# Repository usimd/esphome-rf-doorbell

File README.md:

# ESPHome RF Doorbell

Battery-powered ESPHome doorbell hardware and firmware centered on the current Rev3 base board.

## Current Scope

- `base/` is the active hardware target.
- `esphome/doorbell.yaml` is the active firmware target.
- Rev3 uses ESP32-C6, LTC4079, ISL23315, MAX17260, and ESPHome's built-in `sx126x` support.
- `remote/` is intentionally kept as unfinished WIP hardware. It is not a supported production target.

## Rev3 Hardware Summary

| Ref | Part | Purpose |
|-----|------|---------|
| U1 | LTC4079 | Li-ion charger |
| U3 | TPS63900 | Low-power buck-boost regulator |
| U4 | MAX17260 | Fuel gauge |
| U5 | LTV-354T | Doorbell input optocoupler |
| U6 | G3VM-31DR | Door opener relay |
| U7 | Wio-SX1262 | SX1262 radio module |
| U8 | G3VM-63ER | Bell mute relay |
| U9 | ESP32-C6-MINI-1 | Main MCU |
| U10 | ISL23315 | Digipot for charger control |

The base board already includes an SX126x receive path and that remains part of the intended design, even though the remote side is still unfinished.

## Repository Layout

```text
base/                    Active Rev3 KiCad project
datasheets/              Datasheets and hardware notes used during development
esphome/                 Active ESPHome firmware
esphome/components/      Custom ESPHome components
lib/                     Project KiCad footprints and symbols
remote/                  Unfinished remote hardware kept as WIP
```

## Firmware

The active firmware is in `esphome/doorbell.yaml`: an always-connected Thread SED
with automatic light sleep, targeting ESPHome 2026.11.0b3. WiFi/deep-sleep firmware
remains available in git history.

Implemented custom components:

- `doorbell_controller`: charger control, supply sensing, direct bell mute and light-sleep GPIO wake
- `max17260`: fuel gauge driver with POR handling and learned-parameter persistence

Radio support uses ESPHome's built-in `sx126x` component rather than a custom RF stack.

## Build

Install the pinned beta toolchain, then build:

```bash
.venv/bin/python -m pip install -r esphome/requirements.txt
.venv/bin/esphome compile esphome/doorbell.yaml
```

The configuration expects `esphome/secrets.yaml` to contain a real `thread_tlv`
dataset, API encryption key and OTA password. See [firmware setup](esphome/README.md).

## Status

- Legacy firmware and custom components are removed from the supported path.
- Thread firmware requires hardware bring-up and current measurement before deployment.
- CI builds the Rev3 firmware and the base KiCad project.
- `remote/` remains a hardware placeholder for future work and still contains legacy symbols/footprints inside that WIP design.

## Notes

- The ESP32-C6 pin usage in this design currently triggers ESPHome warnings for USB-Serial-JTAG pins and strapping pins. Those warnings reflect the current hardware choices and should be kept in mind during bring-up.
- `esphome/charging_test.yaml` and `esphome/charging_test_simple.yaml` currently exist as untracked placeholders and are not part of the supported firmware path.

## AISLER discount

In case you want to order this (or any other) project at AISLER, here's a 10€ discount code: `MakeInEurope-ZDCTN`

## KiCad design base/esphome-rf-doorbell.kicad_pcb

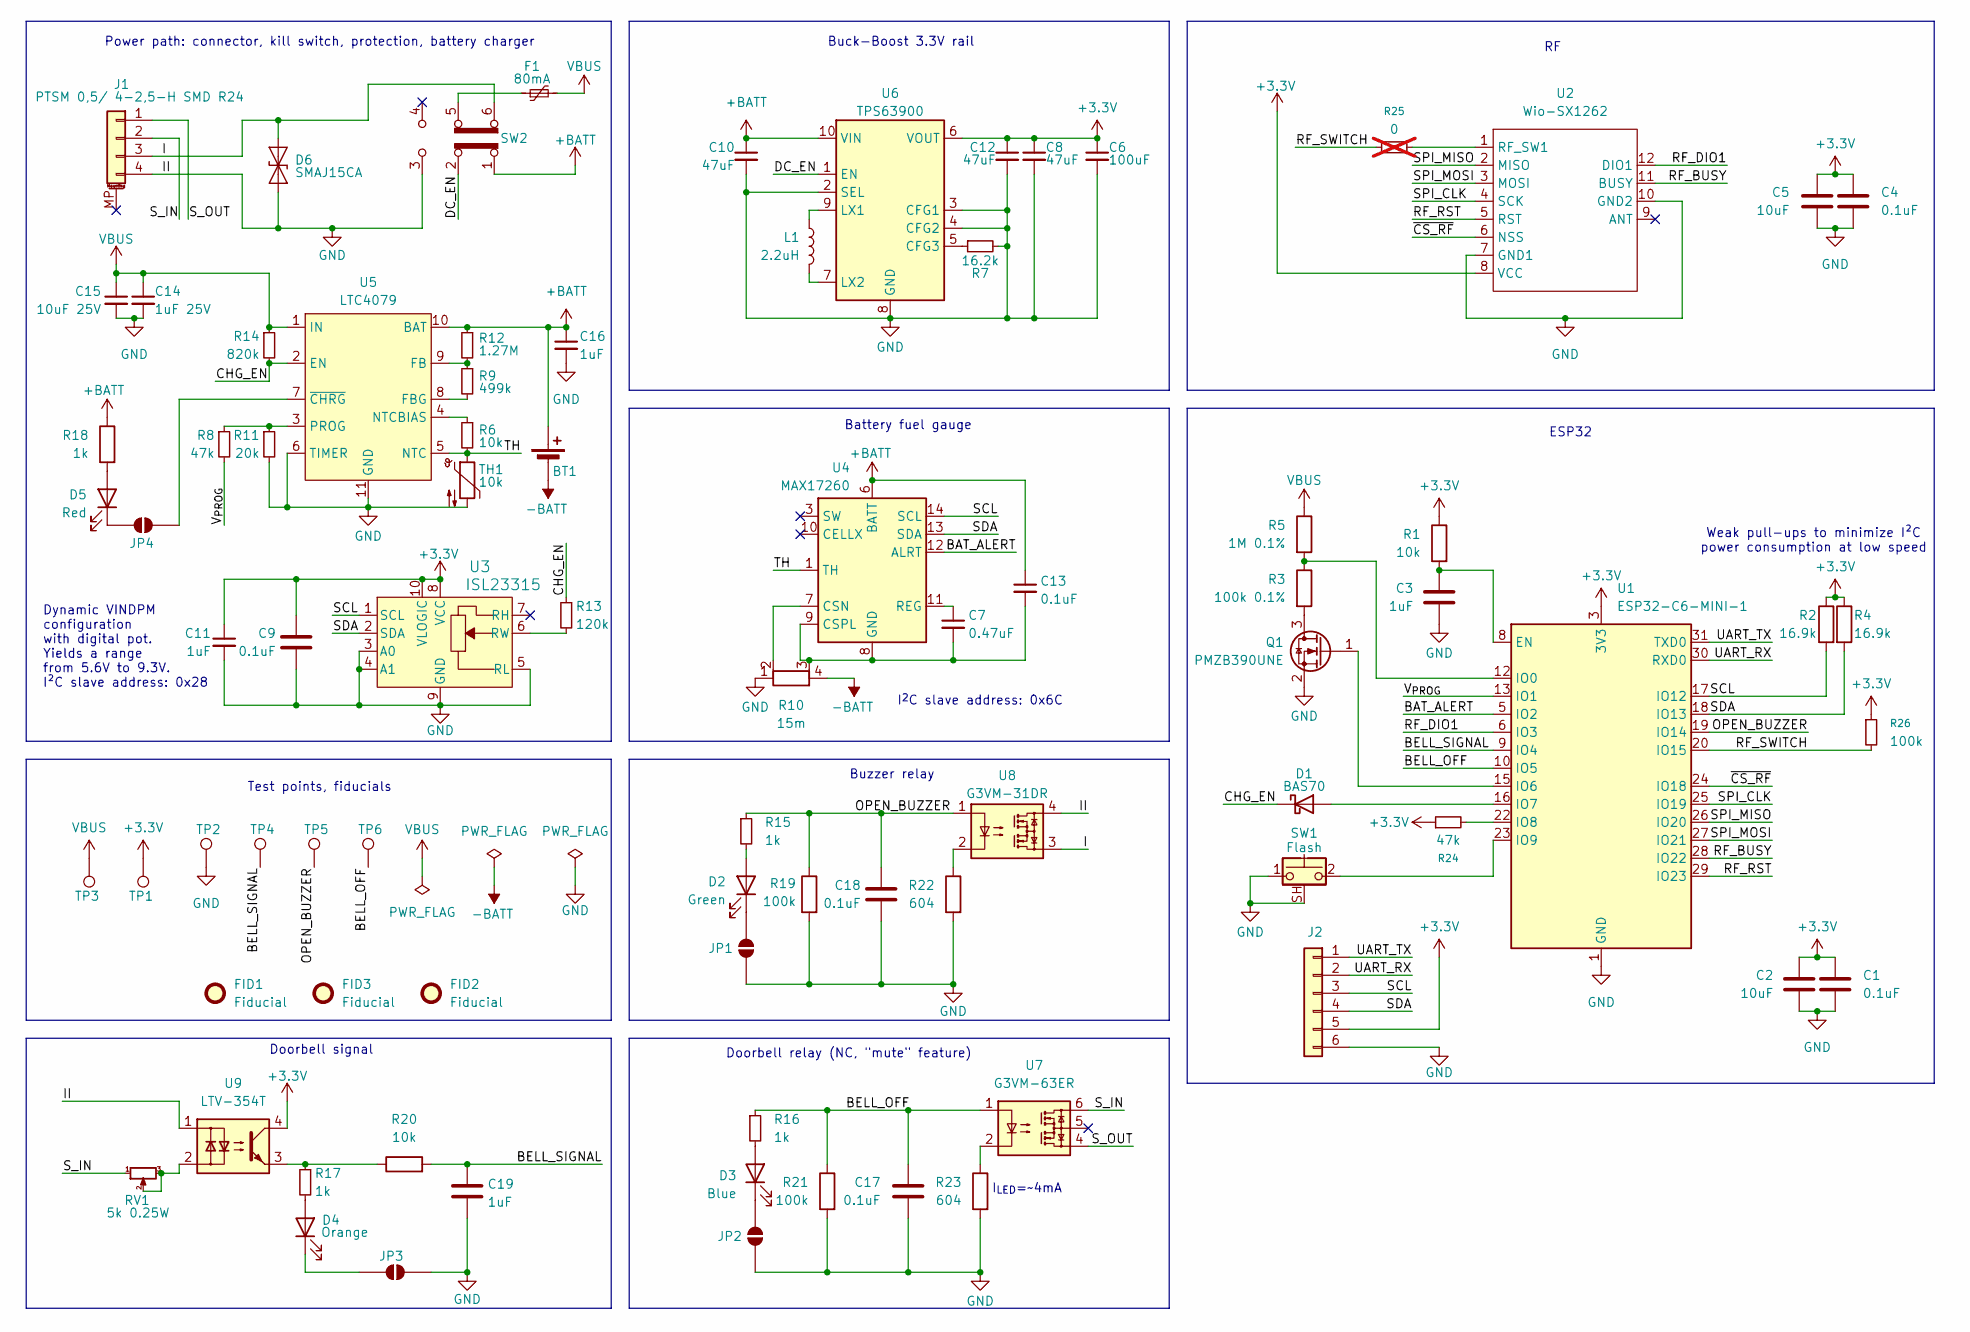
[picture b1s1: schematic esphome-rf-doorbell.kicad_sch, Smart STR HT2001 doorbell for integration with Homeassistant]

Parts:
BT1: Molex_PicoBlade_53261-0271_1x02-1MP_P1.25mm_Horizontal; MPN 532610271
C1, C4, C9, C13, C17, C18: 0.1uF; C_0402_1005Metric
C2, C5: 10uF; C_0603_1608Metric
C3: 1uF; C_0603_1608Metric
C6: 100uF; C_1206_3216Metric
C7: 0.47uF; C_0402_1005Metric
C8, C10, C12: 47uF; C_0805_2012Metric
C11, C16, C19: 1uF; C_0402_1005Metric
C14: 1uF 25V; C_0402_1005Metric
C15: 10uF 25V; C_0603_1608Metric
D1: BAS70; D_SOD-523; MPN BAS7002VH6327XTSA1
D2: Green; LED_0603_1608Metric
D3: Blue; LED_0603_1608Metric
D4: Orange; LED_0603_1608Metric
D5: Red; LED_0603_1608Metric
D6: SMAJ15CA; D_SMA; MPN SMAJ15CA
F1: 80mA; Fuse_0603_1608Metric; MPN SMD0603B008TF
FID1, FID2, FID3: Fiducial; Fiducial_0.5mm_Mask1mm
J1: PTSM 0,5/ 4-2,5-H SMD R24; PHOENIX_1702474; MPN 1702474
J2: Conn_01x06; Connector_PogoClamp_1.27mm
JP1, JP2, JP3, JP4: SolderJumper_2_Open; SolderJumper-2_P1.3mm_Open_RoundedPad1.0x1.5mm
L1: 2.2uH; L_1210_3225Metric; MPN DFE32CAH2R2MR0L
Q1: PMZB390UNE; Diodes_DFN1006-3; MPN PMZB390UNEYL
R1: 10k; R_0603_1608Metric
R2, R4: 16.9k; R_0402_1005Metric
R3: 100k 0.1%; C_0402_1005Metric
R5: 1M 0.1%; C_0402_1005Metric
R6, R20: 10k; R_0402_1005Metric
R7: 16.2k; R_0402_1005Metric
R8: 47k; R_0402_1005Metric
R9: 499k; R_0402_1005Metric
R10: 15m; R_Shunt_D1WRL1206; MPN D1WRL1206L4R015D-T5
R11: 20k; R_0402_1005Metric
R12: 1.27M; R_0402_1005Metric
R13: 120k; R_0402_1005Metric
R14: 820k; R_0805_2012Metric
R15, R16, R17, R18: 1k; R_0402_1005Metric
R19, R21: 100k; R_0402_1005Metric
R22, R23: 604; R_0402_1005Metric
R24: 47k; C_0402_1005Metric
R25: 0; C_0402_1005Metric; not fitted
R26: 100k; C_0402_1005Metric
RV1: 5k 0.25W; Potentiometer_Bourns_3214W_Vertical; MPN 3214W-1-502E
SW1: Flash; SW_SPST_Panasonic_EVQPL_3PL_5PL_PT_A08; MPN TVCU18015BPB
SW2: CL-SB-22A-11T; CL-SB-22A; MPN CL-SB-22A-11T
TH1: 10k; R_0603_1608Metric; MPN NTCS0603E3103FLT
TP1, TP2, TP3, TP4, TP5, TP6: TestPoint; TestPoint_Pad_D1.5mm
U1: ESP32-C6-MINI-1; XCVR_ESP32-C6-MINI-1U-N4; MPN ESP32-C6-MINI-1U-N4
U2: Wio-SX1262; Wio-SX1262 PCB Package; MPN WIO-SX1262
U3: ISL23315; L10_2P1X1P6A_INR; MPN ISL23315TFRUZ-T7A
U4: MAX17260; TDFN-14-1EP_3x3mm_P0.4mm_EP1.78x2.35mm; MPN MAX17260SETD+
U5: LTC4079; DFN-10-1EP_3x3mm_P0.5mm_EP1.65x2.38mm; MPN LTC4079EDD#TRPBF
U6: TPS63900; WSON-10-1EP_2.5x2.5mm_P0.5mm_EP1.2x2mm_ThermalVias; MPN TPS63900DSKR
U7: G3VM-63ER; G3VM-21ER; MPN G3VM-63ER
U8: G3VM-31DR; G3VM-21DR; MPN G3VM-31DR
U9: LTV-354T; SO-4_4.4x3.6mm_P2.54mm; MPN LTV-354T

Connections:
+3.3V: C1.1, C2.1, C4.1, C5.1, C6.1, C8.1, C9.1, C11.1, C12.1, J2.5, R1.1, R2.1, R4.1, R24.1, R26.1, TP1.1 (1_1), U1.3 (3V3), U2.8 (VCC), U3.8 (VCC), U3.10 (VLOGIC), U6.6 (VOUT), U9.4
+BATT: BT1.1 (+), C10.1, C13.1, C16.1, R12.1, R18.1, SW2.1 (A), U4.6 (BATT), U5.10 (BAT), U6.10 (VIN)
-BATT: BT1.2 (-), R10.4
/BAT_ALERT: U1.5 (IO2), U4.12 (ALRT)
/BELL_OFF: C17.1, R16.1, R21.1, TP6.1 (1_1), U1.10 (IO5), U7.1
/BELL_SIGNAL: C19.1, R20.2, TP4.1 (1_1), U1.9 (IO4)
/CHG_EN: D1.1 (K), R13.1, R14.2, U5.2 (EN)
/DC_EN: SW2.2 (B), U6.1 (EN)
/I: D6.2 (A2), J1.3, SW2.6 (C), U8.3
/OPEN_BUZZER: C18.1, R15.1, R19.1, TP5.1 (1_1), U1.19 (IO14), U8.1
/RF_BUSY: U1.28 (IO22), U2.11 (BUSY)
/RF_DIO1: U1.6 (IO3), U2.12 (DIO1)
/RF_RST: U1.29 (IO23), U2.5 (RST)
/RF_SWITCH: R25.1, R26.2, U1.20 (IO15)
/SCL: J2.3, R2.2, U1.17 (IO12), U3.1 (SCL), U4.14 (SCL)
/SDA: J2.4, R4.2, U1.18 (IO13), U3.2 (SDA), U4.13 (SDA)
/SPI_CLK: U1.25 (IO19), U2.4 (SCK)
/SPI_MISO: U1.26 (IO20), U2.2 (MISO)
/SPI_MOSI: U1.27 (IO21), U2.3 (MOSI)
/S_IN: J1.2, RV1.1, U7.6
/S_OUT: J1.1, U7.4
/TH: R6.2, TH1.1, U4.1 (TH), U5.5 (NTC)
/UART_RX: J2.2, U1.30 (RXD0)
/UART_TX: J2.1, U1.31 (TXD0)
/V_{PROG}: R8.2, U1.13 (IO1)
/~CS_RF: U1.24 (IO18), U2.6 (NSS)
GND: C1.2, C2.2, C3.2, C4.2, C5.2, C6.2, C8.2, C9.2, C10.2, C11.2, C12.2, C14.2, C15.2, C16.2, C17.2, C18.2, C19.2, D6.1 (A1), J1.4, J2.6, JP1.1 (A), JP2.1 (A), JP3.2 (B), Q1.2 (S), R7.2, R10.1, R11.2, R19.2, R21.2, R22.2, R23.2, SW1.1, SW1.SH (B), SW2.3 (C), TH1.2, TP2.1 (1_1), U1.1 (GND), U1.2 (GND), U1.11 (GND), U1.14 (GND), U1.36 (GND), U1.37 (GND), U1.38 (GND), U1.39 (GND), U1.40 (GND), U1.41 (GND), U1.42 (GND), U1.43 (GND), U1.44 (GND), U1.45 (GND), U1.46 (GND), U1.47 (GND), U1.48 (GND), U1.49 (GND), U1.50 (GND), U1.51 (GND), U1.52 (GND), U1.53 (GND), U2.7 (GND1), U2.10 (GND2), U3.3 (A0), U3.4 (A1), U3.5 (RL), U3.9 (GND), U5.6 (TIMER), U5.11 (GND), U6.2 (SEL), U6.3 (CFG1), U6.4 (CFG2), U6.8 (GND), U6.11 (GND), U8.4, U9.1
unnamed: D1.2 (A), U1.16 (IO7)
unnamed: D2.2 (A), R15.2
unnamed: D2.1 (K), JP1.2 (B)
unnamed: D3.2 (A), R16.2
unnamed: D3.1 (K), JP2.2 (B)
unnamed: D4.2 (A), R17.2
unnamed: D4.1 (K), JP3.1 (A)
unnamed: D5.2 (A), R18.2
unnamed: D5.1 (K), JP4.2 (B)
unnamed: F1.1, SW2.5 (B)
unnamed: JP4.1 (A), U5.7 (~CHRG)
unnamed: Q1.3 (D), R3.2
unnamed: Q1.1 (G), U1.15 (IO6)
unnamed: R17.1, R20.1, U9.3
unnamed: R22.1, U8.2
unnamed: R23.1, U7.2
unnamed: RV1.2, RV1.3, U9.2
unnamed: C3.1, R1.2, U1.8 (EN)
unnamed: R3.1, R5.2, U1.12 (IO0)
unnamed: R24.2, U1.22 (IO8)
unnamed: SW1.2, U1.23 (IO9)
unnamed: R25.2, U2.1 (RF_SW1)
unnamed: R13.2, U3.6 (RW)
unnamed: R10.2, U4.7 (CSN)
unnamed: C7.2, C13.2, R10.3, U4.8 (GND), U4.9 (CSPL), U4.15 (GND)
unnamed: C7.1, U4.11 (REG)
unnamed: R9.1, R12.2, U5.9 (FB)
unnamed: R9.2, U5.8 (FBG)
unnamed: R6.1, U5.4 (NTCBIAS)
unnamed: R8.1, R11.1, U5.3 (PROG)
unnamed: R7.1, U6.5 (CFG3)
unnamed: L1.1, U6.9 (LX1)
unnamed: L1.2, U6.7 (LX2)
VBUS: C14.1, C15.1, F1.2, R5.1, R14.1, TP3.1 (1_1), U5.1 (IN)

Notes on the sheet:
Dynamic VINDPM configuration with digital pot. Yields a range from 5.6V to 9.3V. I²C slave address: 0x28
Test points, fiducials
Battery fuel gauge
ESP32
Weak pull-ups to minimize I²C power consumption at low speed
Doorbell signal
I_{LED}=~4mA
Buzzer relay
Doorbell relay (NC, "mute" feature)
Buck-Boost 3.3V rail
Power path: connector, kill switch, protection, battery charger
I^{2}C slave address: 0x6C

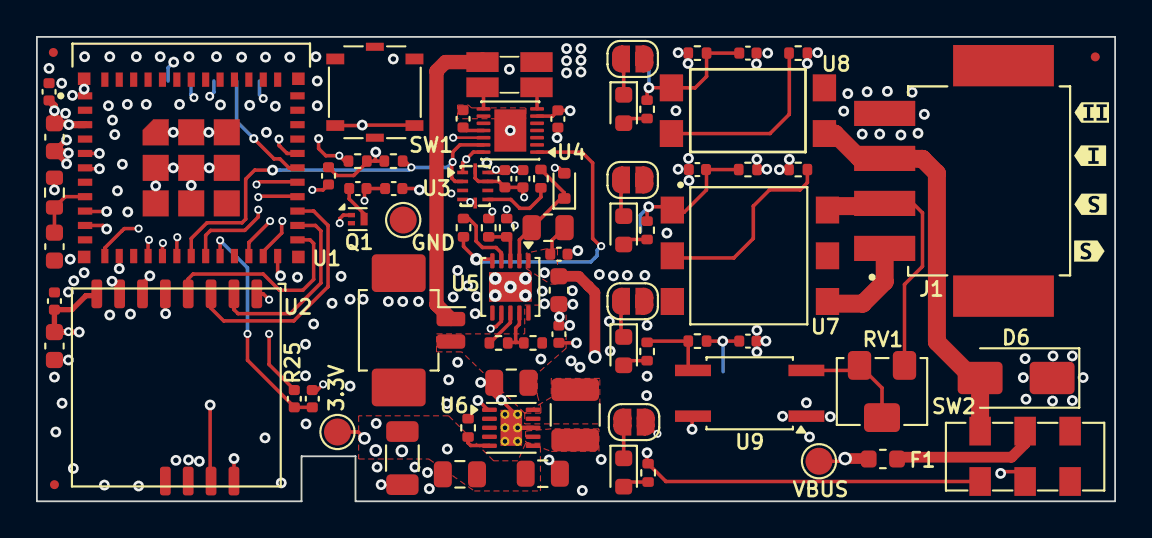
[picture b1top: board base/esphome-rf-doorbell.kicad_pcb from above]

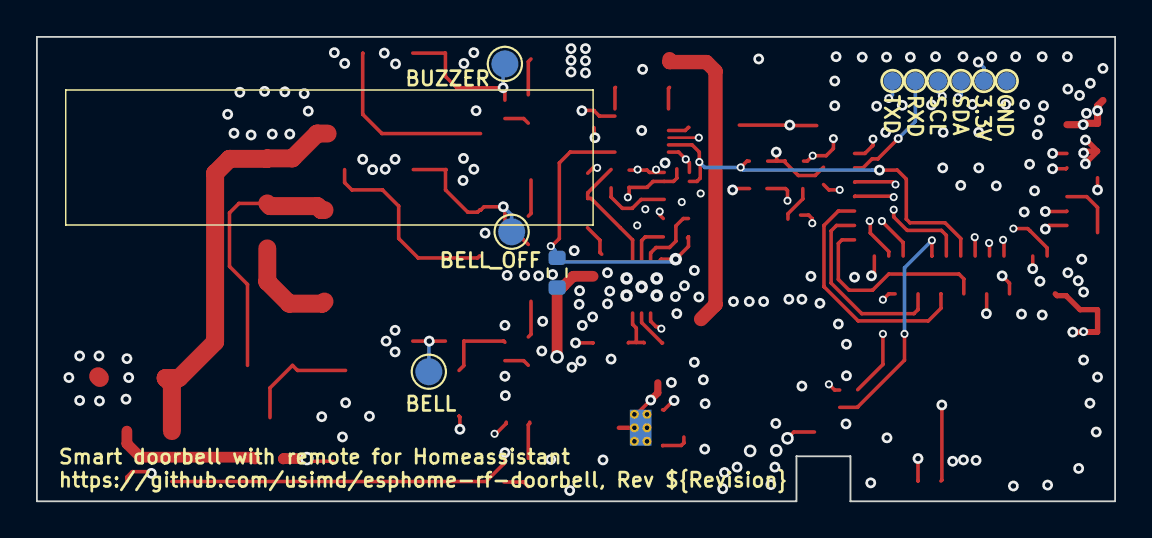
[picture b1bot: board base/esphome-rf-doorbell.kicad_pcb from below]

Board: 4 copper layers, 59.9 x 25.8 mm, 87 parts (5 on the bottom side), 61 nets.

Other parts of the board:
kibuzzard-696E5F1B: G***; kibuzzard-696E5F1B
kibuzzard-696E5F3B: G***; kibuzzard-696E5F3B
kibuzzard-696E5F26: G***; kibuzzard-696E5F26
kibuzzard-696E5F32: G***; kibuzzard-696E5F32

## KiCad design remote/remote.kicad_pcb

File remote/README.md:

# Remote WIP

`remote/` is intentionally kept as unfinished hardware work.

- It is not a supported production target.
- The old remote firmware implementation was removed.
- The current schematic and PCB may still contain legacy placeholder parts from earlier RF exploration.
- Keep this directory as hardware WIP until the remote architecture is redesigned around the current project direction.

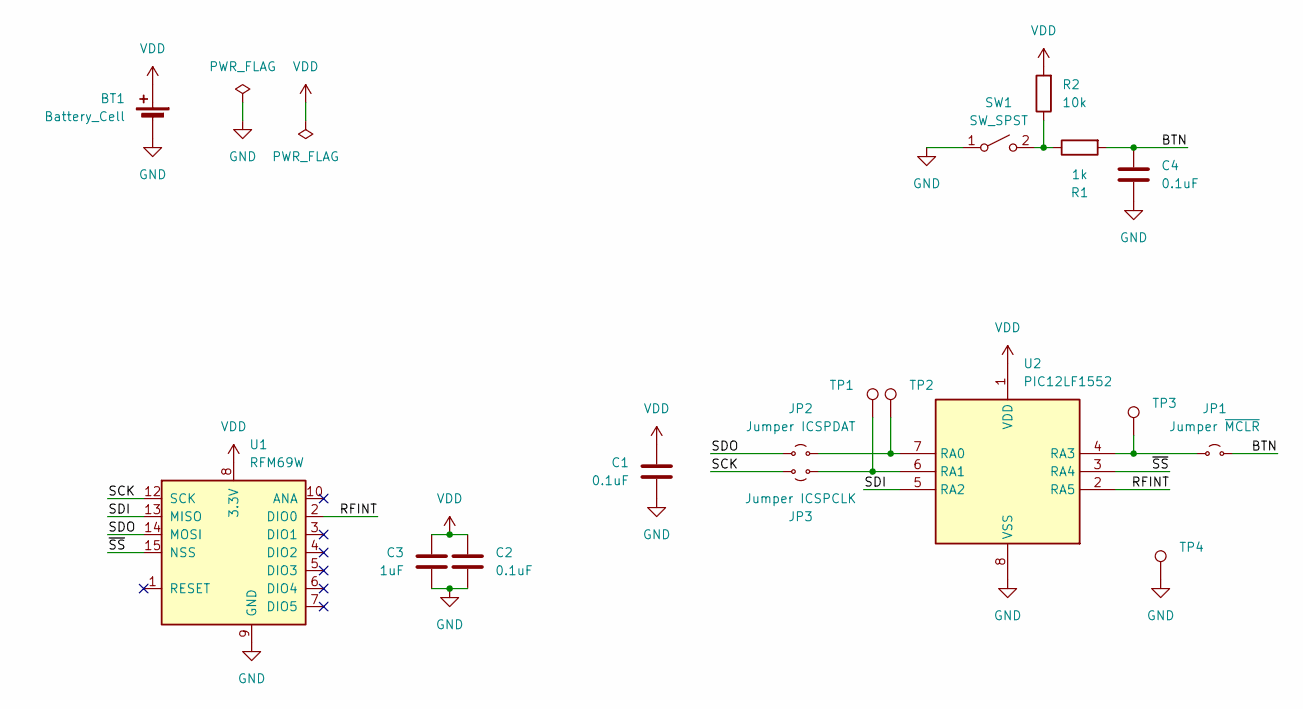
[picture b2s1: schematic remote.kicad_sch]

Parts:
BT1: Battery_Cell; BatteryHolder_Keystone_1060_1x2032
C1, C2, C4: 0.1uF; C_0603_1608Metric_Pad1.08x0.95mm_HandSolder
C3: 1uF; C_0603_1608Metric_Pad1.08x0.95mm_HandSolder
JP1: Jumper ~{MCLR}; SolderJumper-2_P1.3mm_Open_RoundedPad1.0x1.5mm
JP2: Jumper ICSPDAT; SolderJumper-2_P1.3mm_Open_RoundedPad1.0x1.5mm
JP3: Jumper ICSPCLK; SolderJumper-2_P1.3mm_Open_RoundedPad1.0x1.5mm
R1: 1k; R_0603_1608Metric_Pad0.98x0.95mm_HandSolder
R2: 10k; R_0603_1608Metric_Pad0.98x0.95mm_HandSolder
SW1: SW_SPST; SW_SPST_Panasonic_EVQPL_3PL_5PL_PT_A15
TP1, TP2, TP3, TP4: TestPoint; TestPoint_Keystone_5000-5004_Miniature
U1: RFM69W; HOPERF_RFM69HW
U2: PIC12LF1552; MSOP-8_3x3mm_P0.65mm

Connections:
/BTN: C4.1, JP1.2 (B), R1.2
/RFINT: U1.2 (DIO0), U2.2 (RA5)
/SCK: JP3.1 (A), U1.12 (SCK)
/SDI: U1.13 (MISO), U2.5 (RA2)
/SDO: JP2.1 (A), U1.14 (MOSI)
/~SS: U1.15 (NSS), U2.3 (RA4)
GND: BT1.2 (-), C1.2, C2.2, C3.2, C4.2, SW1.1 (A), TP4.1, U1.9 (GND), U1.11 (GND), U2.8 (VSS)
unnamed: JP1.1 (A), TP3.1, U2.4 (RA3)
unnamed: JP2.2 (B), TP2.1, U2.7 (RA0)
unnamed: JP3.2 (B), TP1.1, U2.6 (RA1)
unnamed: R1.1, R2.1, SW1.2 (B)
VDD: BT1.1 (+), C1.1, C2.1, C3.1, R2.2, U1.8 (3.3V), U2.1 (VDD)

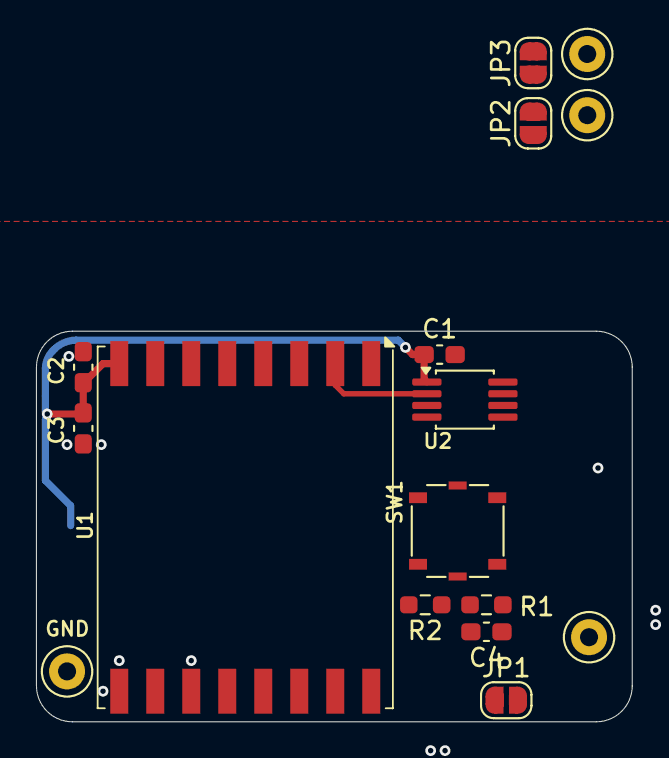
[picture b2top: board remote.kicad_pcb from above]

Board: 2 copper layers, 33.1 x 21.7 mm, 17 parts (1 on the bottom side), 12 nets.

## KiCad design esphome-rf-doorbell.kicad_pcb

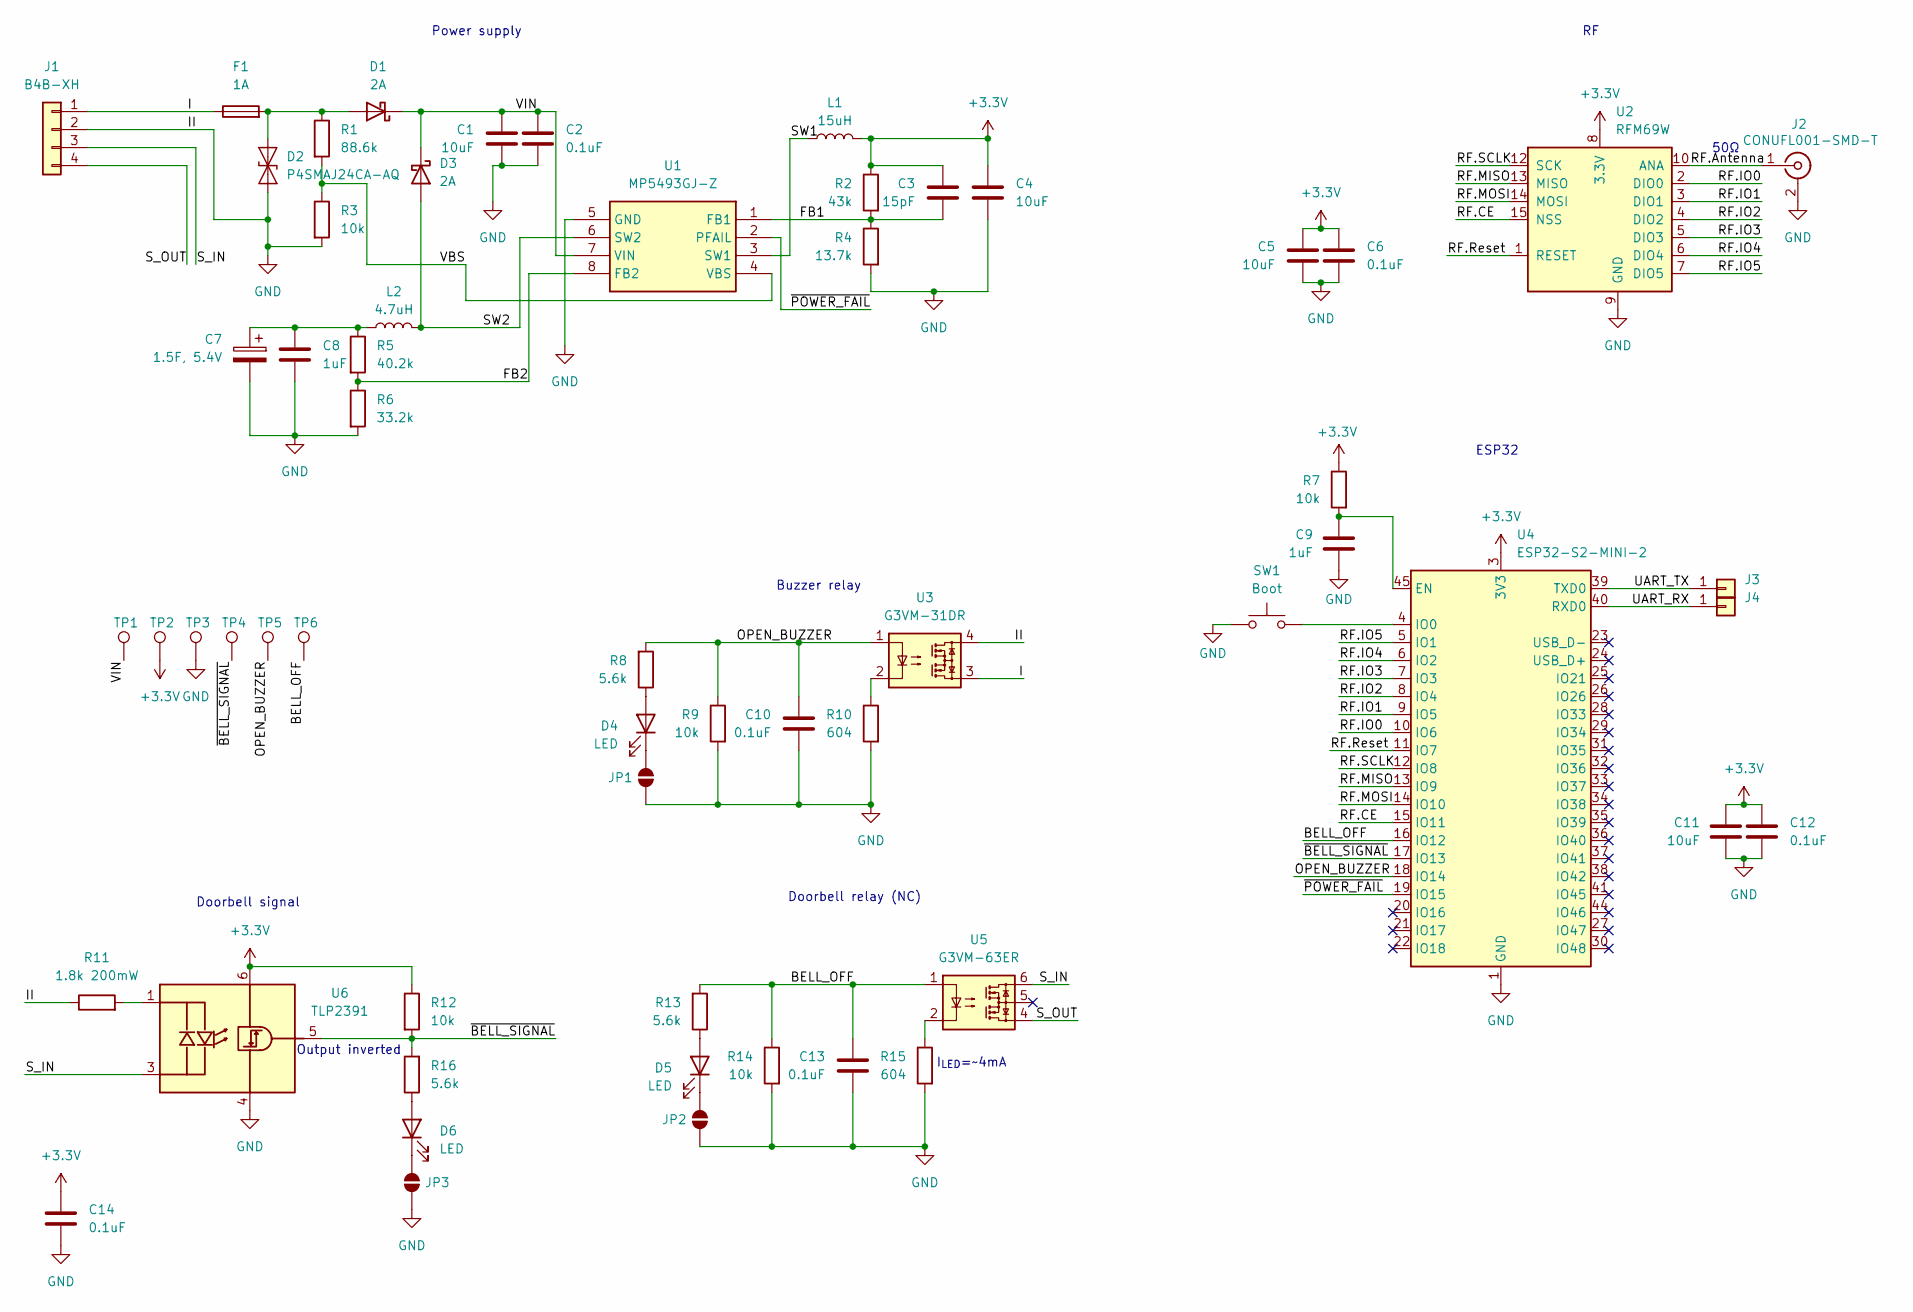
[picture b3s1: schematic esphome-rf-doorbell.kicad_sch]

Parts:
C1: 10uF; C_0805_2012Metric
C2, C6, C10, C12, C13, C14: 0.1uF; C_0402_1005Metric
C3: 15pF; R_0402_1005Metric
C4, C5, C11: 10uF; C_0603_1608Metric
C7: 1.5F, 5.4V; PHV5R4V155R; MPN PHV-5R4V155-R
C8: 1uF; R_0603_1608Metric
C9: 1uF; C_0603_1608Metric
D1, D3: 2A; D_SMA; MPN STPS2L60A
D2: P4SMAJ24CA-AQ; D_SMA; MPN P4SMAJ24CA-AQ
D4, D5, D6: LED; LED_0603_1608Metric
F1: 1A; Fuse_0603_1608Metric; MPN 3412.0115.11
J1: B4B-XH; JST_XH_B4B-XH-A_1x04_P2.50mm_Vertical
J2: CONUFL001-SMD-T; U.FL_Hirose_U.FL-R-SMT-1_Vertical; MPN CONUFL001-SMD-T; LCSC Part # C22418213
J3, J4: Conn_01x01; TestPoint_Keystone_5000-5004_Miniature
JP1, JP2, JP3: SolderJumper_2_Open; SolderJumper-2_P1.3mm_Bridged_RoundedPad1.0x1.5mm
L1: 15uH; L_APV_ANR8040; MPN DJNR8040-150
L2: 4.7uH; L_APV_APH1040; MPN HPI1040-150
R1: 88.6k; R_0603_1608Metric
R2: 43k; R_0603_1608Metric
R3, R7, R9, R12, R14: 10k; R_0603_1608Metric
R4: 13.7k; R_0603_1608Metric
R5: 40.2k; R_0402_1005Metric
R6: 33.2k; R_0603_1608Metric
R8, R13, R16: 5.6k; R_0603_1608Metric
R10, R15: 604; R_0402_1005Metric_Pad0.72x0.64mm_HandSolder
R11: 1.8k 200mW; R_0603_1608Metric
SW1: Boot; SW_SPST_PTS647_Sx50; MPN TS110926045
TP1, TP2, TP3, TP4, TP5, TP6: TestPoint; TestPoint_Pad_D1.5mm
U1: MP5493GJ-Z; SOT65P280X100-8N; Manufacturer_Part_Number MP5493GJ-Z
U2: RFM69W; HOPERF_RFM69HW
U3: G3VM-31DR; SMDIP-4_W7.62mm
U4: ESP32-S2-MINI-2; ESP32-S2-MINI-1
U5: G3VM-63ER; SMDIP-6_W7.62mm; MPN G3VM-63ER
U6: TLP2391; OPTO_TLP2367_TPR_E; MPN TLP2391

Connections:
+3.3V: C3.1, C4.1, C5.1, C6.1, C11.1, C12.1, C14.1, L1.2, R2.1, R7.1, R12.1, TP2.1, U2.8 (3.3V), U4.3 (3V3), U6.6 (VDD)
/BELL_OFF: C13.1, R13.2, R14.1, TP6.1, U4.16 (IO12), U5.1
/FB1: C3.2, R2.2, R4.1, U1.1 (FB1)
/FB2: R5.2, R6.1, U1.8 (FB2)
/I: F1.1, J1.1, U3.3
/OPEN_BUZZER: C10.1, R8.2, R9.1, TP5.1, U3.1, U4.18 (IO14)
/RF.Antenna: J2.1 (In), U2.10 (ANA)
/RF.CE: U2.15 (NSS), U4.15 (IO11)
/RF.IO0: U2.2 (DIO0), U4.10 (IO6)
/RF.IO1: U2.3 (DIO1), U4.9 (IO5)
/RF.IO2: U2.4 (DIO2), U4.8 (IO4)
/RF.IO3: U2.5 (DIO3), U4.7 (IO3)
/RF.IO4: U2.6 (DIO4), U4.6 (IO2)
/RF.IO5: U2.7 (DIO5), U4.5 (IO1)
/RF.MISO: U2.13 (MISO), U4.13 (IO9)
/RF.MOSI: U2.14 (MOSI), U4.14 (IO10)
/RF.Reset: U2.1 (RESET), U4.11 (IO7)
/RF.SCLK: U2.12 (SCK), U4.12 (IO8)
/SW1: L1.1, U1.3 (SW1)
/SW2: D3.2 (A), L2.2, U1.6 (SW2)
/S_IN: J1.3, U5.6, U6.3 (K)
/S_OUT: J1.4, U5.4
/UART_RX: J4.1, U4.40 (RXD0)
/UART_TX: J3.1, U4.39 (TXD0)
/VBS: R1.2, R3.1, U1.4 (VBS)
/VIN: C1.1, C2.1, D1.1 (K), D3.1 (K), TP1.1, U1.7 (VIN)
/~BELL_SIGNAL: R12.2, R16.2, TP4.1, U4.17 (IO13), U6.5 (VO)
/~POWER_FAIL: U1.2 (PFAIL), U4.19 (IO15)
GND: C1.2, C2.2, C4.2, C5.2, C6.2, C7.2, C8.2, C9.2, C10.2, C11.2, C12.2, C13.2, C14.2, D2.1 (A1), J1.2, J2.2 (Ext), JP1.1 (A), JP2.1 (A), JP3.1 (A), R3.2, R4.2, R6.2, R9.2, R10.2, R11.1, R14.2, R15.2, SW1.1, TP3.1, U1.5 (GND), U2.9 (GND), U2.11 (GND), U3.4, U4.1 (GND), U4.2 (GND), U4.42 (GND), U4.43 (GND), U4.46 (GND), U4.47 (GND), U4.48 (GND), U4.49 (GND), U4.50 (GND), U4.51 (GND), U4.52 (GND), U4.53 (GND), U4.54 (GND), U4.55 (GND), U4.56 (GND), U4.57 (GND), U4.58 (GND), U4.59 (GND), U4.60 (GND), U4.61 (GND), U4.62 (GND), U4.63 (GND), U4.64 (GND), U4.65 (GND), U6.4 (GND)
unnamed: C7.1, C8.1, L2.1, R5.1
unnamed: D1.2 (A), D2.2 (A2), F1.2, R1.1
unnamed: D4.2 (A), R8.1
unnamed: D4.1 (K), JP1.2 (B)
unnamed: D5.2 (A), R13.1
unnamed: D5.1 (K), JP2.2 (B)
unnamed: D6.2 (A), R16.1
unnamed: D6.1 (K), JP3.2 (B)
unnamed: R10.1, U3.2
unnamed: R15.1, U5.2
unnamed: C9.1, R7.2, U4.45 (EN)
unnamed: SW1.2, U4.4 (IO0)
unnamed: R11.2, U6.1 (A)

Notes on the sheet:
ESP32
Doorbell signal
I_{LED}=~4mA
Buzzer relay
Doorbell relay (NC)
Output inverted
Power supply
50Ω

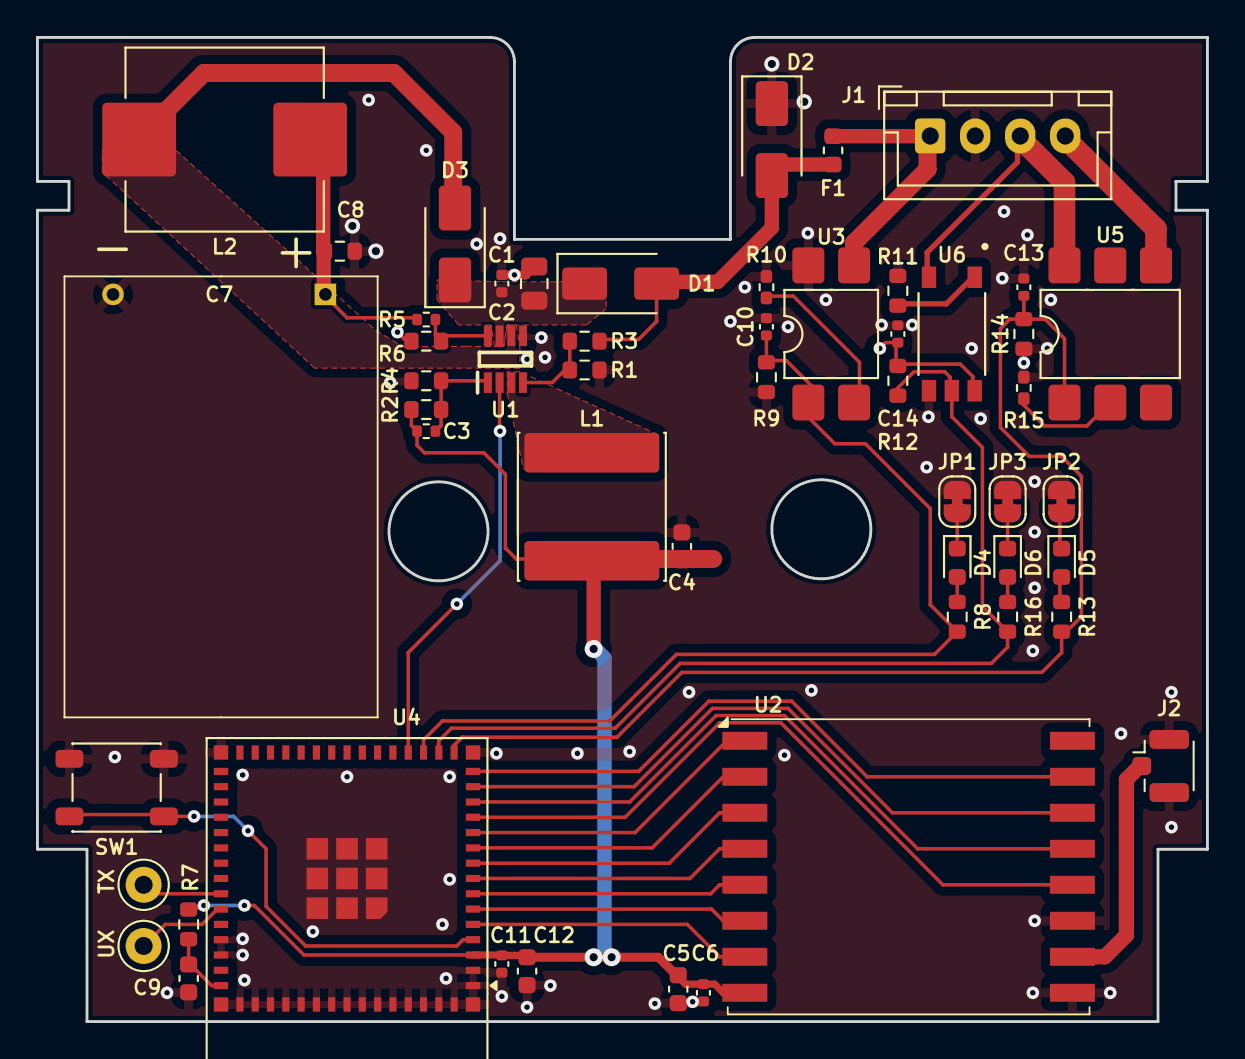
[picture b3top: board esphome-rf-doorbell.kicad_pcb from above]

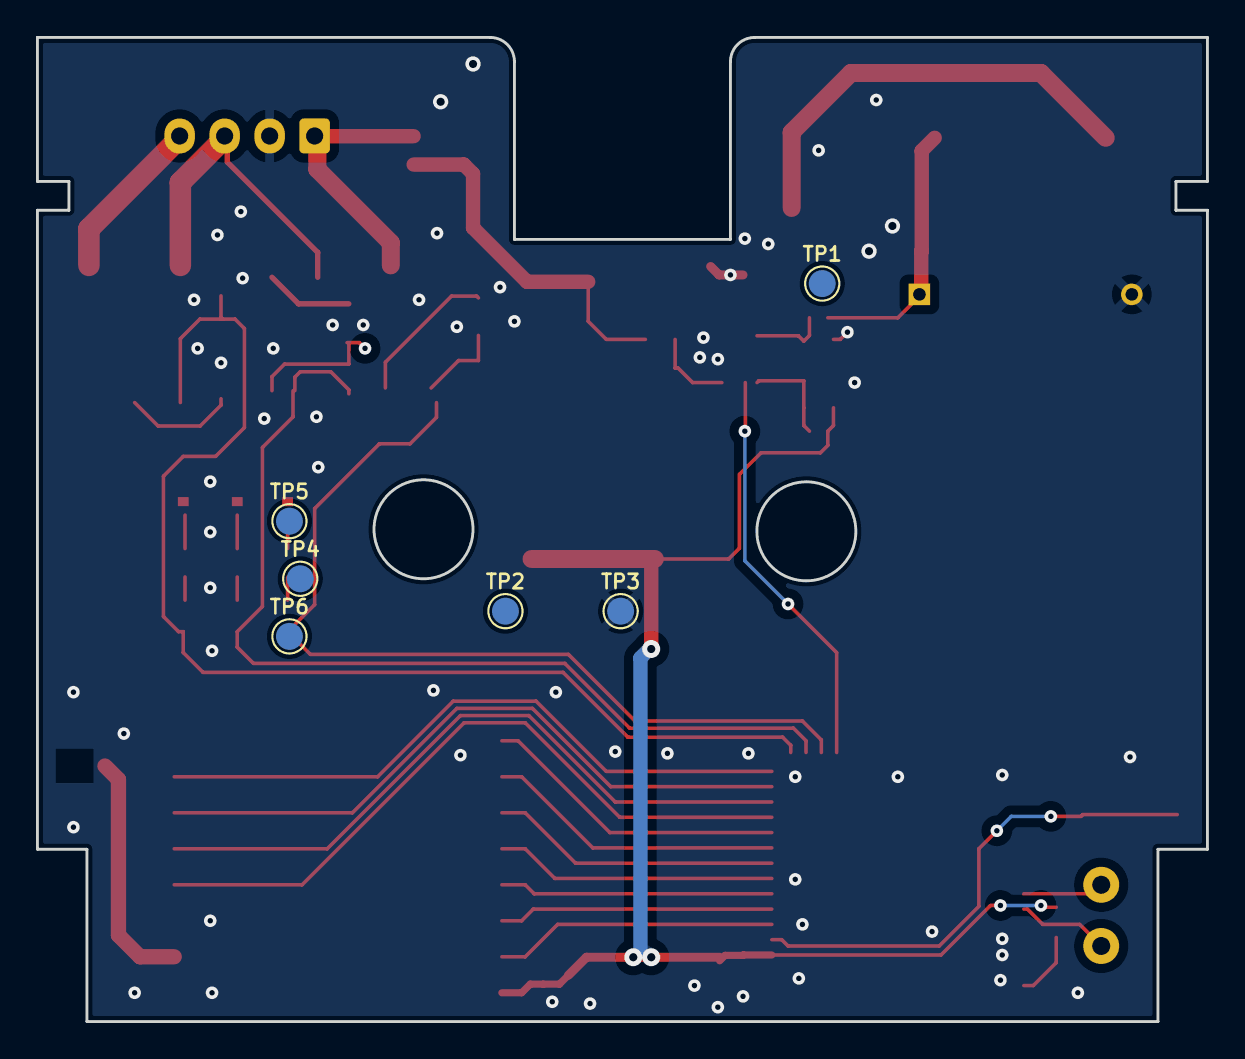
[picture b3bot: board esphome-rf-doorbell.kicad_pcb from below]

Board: 2 copper layers, 65.0 x 54.7 mm, 59 parts (6 on the bottom side), 42 nets.

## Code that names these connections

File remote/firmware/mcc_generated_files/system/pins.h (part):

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// get/set IO_RA0 aliases
#define IO_RA0_TRIS                 TRISAbits.TRISA0
#define IO_RA0_LAT                  LATAbits.LATA0
#define IO_RA0_PORT                 PORTAbits.RA0
#define IO_RA0_WPU                  WPUAbits.WPUA0
#define IO_RA0_OD                   ODCONAbits.
#define IO_RA0_ANS                  ANSELAbits.ANSA0
#define IO_RA0_SetHigh()            do { LATAbits.LATA0 = 1; } while(0)
#define IO_RA0_SetLow()             do { LATAbits.LATA0 = 0; } while(0)
#define IO_RA0_Toggle()             do { LATAbits.LATA0 = ~LATAbits.LATA0; } while(0)
#define IO_RA0_GetValue()           PORTAbits.RA0
#define IO_RA0_SetDigitalInput()    do { TRISAbits.TRISA0 = 1; } while(0)
#define IO_RA0_SetDigitalOutput()   do { TRISAbits.TRISA0 = 0; } while(0)
#define IO_RA0_SetPullup()          do { WPUAbits.WPUA0 = 1; } while(0)
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// get/set IO_RA1 aliases
#define IO_RA1_TRIS                 TRISAbits.TRISA1
#define IO_RA1_LAT                  LATAbits.LATA1
#define IO_RA1_PORT                 PORTAbits.RA1
#define IO_RA1_WPU                  WPUAbits.WPUA1
#define IO_RA1_OD                   ODCONAbits.
#define IO_RA1_ANS                  ANSELAbits.ANSA1
#define IO_RA1_SetHigh()            do { LATAbits.LATA1 = 1; } while(0)
#define IO_RA1_SetLow()             do { LATAbits.LATA1 = 0; } while(0)
#define IO_RA1_Toggle()             do { LATAbits.LATA1 = ~LATAbits.LATA1; } while(0)
#define IO_RA1_GetValue()           PORTAbits.RA1
#define IO_RA1_SetDigitalInput()    do { TRISAbits.TRISA1 = 1; } while(0)
#define IO_RA1_SetDigitalOutput()   do { TRISAbits.TRISA1 = 0; } while(0)
#define IO_RA1_SetPullup()          do { WPUAbits.WPUA1 = 1; } while(0)
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// get/set IO_RA2 aliases
#define IO_RA2_TRIS                 TRISAbits.TRISA2
#define IO_RA2_LAT                  LATAbits.LATA2
#define IO_RA2_PORT                 PORTAbits.RA2
#define IO_RA2_WPU                  WPUAbits.WPUA2
#define IO_RA2_OD                   ODCONAbits.
#define IO_RA2_ANS                  ANSELAbits.ANSA2
#define IO_RA2_SetHigh()            do { LATAbits.LATA2 = 1; } while(0)
#define IO_RA2_SetLow()             do { LATAbits.LATA2 = 0; } while(0)
#define IO_RA2_Toggle()             do { LATAbits.LATA2 = ~LATAbits.LATA2; } while(0)
#define IO_RA2_GetValue()           PORTAbits.RA2
#define IO_RA2_SetDigitalInput()    do { TRISAbits.TRISA2 = 1; } while(0)
#define IO_RA2_SetDigitalOutput()   do { TRISAbits.TRISA2 = 0; } while(0)
#define IO_RA2_SetPullup()          do { WPUAbits.WPUA2 = 1; } while(0)
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// get/set IO_RA3 aliases
#define BTN_TRIS                 TRISAbits.TRISA3
#define BTN_LAT                  LATAbits.
#define BTN_PORT                 PORTAbits.RA3
#define BTN_WPU                  WPUAbits.WPUA3
#define BTN_OD                   ODCONAbits.
#define BTN_ANS                  ANSELAbits.
#define BTN_SetHigh()            do { LATAbits. = 1; } while(0)
#define BTN_SetLow()             do { LATAbits. = 0; } while(0)
#define BTN_Toggle()             do { LATAbits. = ~LATAbits.; } while(0)
#define BTN_GetValue()           PORTAbits.RA3
#define BTN_SetDigitalInput()    do { TRISAbits.TRISA3 = 1; } while(0)
#define BTN_SetDigitalOutput()   do { TRISAbits.TRISA3 = 0; } while(0)
#define BTN_SetPullup()          do { WPUAbits.WPUA3 = 1; } while(0)
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// get/set IO_RA4 aliases
#define CS_TRIS                 TRISAbits.TRISA4
#define CS_LAT                  LATAbits.LATA4
#define CS_PORT                 PORTAbits.RA4
#define CS_WPU                  WPUAbits.WPUA4
#define CS_OD                   ODCONAbits.
#define CS_ANS                  ANSELAbits.ANSA4
#define CS_SetHigh()            do { LATAbits.LATA4 = 1; } while(0)
#define CS_SetLow()             do { LATAbits.LATA4 = 0; } while(0)
#define CS_Toggle()             do { LATAbits.LATA4 = ~LATAbits.LATA4; } while(0)
#define CS_GetValue()           PORTAbits.RA4
#define CS_SetDigitalInput()    do { TRISAbits.TRISA4 = 1; } while(0)
#define CS_SetDigitalOutput()   do { TRISAbits.TRISA4 = 0; } while(0)
#define CS_SetPullup()          do { WPUAbits.WPUA4 = 1; } while(0)
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// get/set IO_RA5 aliases
#define RFINT_TRIS                 TRISAbits.TRISA5
#define RFINT_LAT                  LATAbits.LATA5
#define RFINT_PORT                 PORTAbits.RA5
#define RFINT_WPU                  WPUAbits.WPUA5
#define RFINT_OD                   ODCONAbits.
#define RFINT_ANS                  ANSELAbits.ANSA5
#define RFINT_SetHigh()            do { LATAbits.LATA5 = 1; } while(0)
#define RFINT_SetLow()             do { LATAbits.LATA5 = 0; } while(0)
#define RFINT_Toggle()             do { LATAbits.LATA5 = ~LATAbits.LATA5; } while(0)
#define RFINT_GetValue()           PORTAbits.RA5
#define RFINT_SetDigitalInput()    do { TRISAbits.TRISA5 = 1; } while(0)
#define RFINT_SetDigitalOutput()   do { TRISAbits.TRISA5 = 0; } while(0)
#define RFINT_SetPullup()          do { WPUAbits.WPUA5 = 1; } while(0)
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
/**
 * @ingroup  pinsdriver
 * @brief Interrupt on Change Handler for the BTN pin functionality
 * @param none
 * @return none
 */
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
/**
 * @ingroup  pinsdriver
 * @brief Interrupt Handler Setter for BTN pin interrupt-on-change functionality.
 *        Allows selecting an interrupt handler for BTN at application runtime.
 * @pre Pins intializer called
 * @param InterruptHandler function pointer.
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
/**
 * @ingroup  pinsdriver
 * @brief Dynamic Interrupt Handler for BTN pin.
 *        This is a dynamic interrupt handler to be used together with the BTN_SetInterruptHandler() method.
 *        This handler is called every time the BTN ISR is executed and allows any function to be registered at runtime.
 * @pre Pins intializer called
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
/**
 * @ingroup  pinsdriver
 * @brief Default Interrupt Handler for BTN pin. 
 *        This is a predefined interrupt handler to be used together with the BTN_SetInterruptHandler() method.
 *        This handler is called every time the BTN ISR is executed. 
 * @pre Pins intializer called
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
/**
 * @ingroup  pinsdriver
 * @brief Interrupt on Change Handler for the RFINT pin functionality
 * @param none
 * @return none
 */
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
/**
 * @ingroup  pinsdriver
 * @brief Interrupt Handler Setter for RFINT pin interrupt-on-change functionality.
 *        Allows selecting an interrupt handler for RFINT at application runtime.
 * @pre Pins intializer called
 * @param InterruptHandler function pointer.
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
/**
 * @ingroup  pinsdriver
 * @brief Dynamic Interrupt Handler for RFINT pin.
 *        This is a dynamic interrupt handler to be used together with the RFINT_SetInterruptHandler() method.
 *        This handler is called every time the RFINT ISR is executed and allows any function to be registered at runtime.
 * @pre Pins intializer called
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
/**
 * @ingroup  pinsdriver
 * @brief Default Interrupt Handler for RFINT pin. 
 *        This is a predefined interrupt handler to be used together with the RFINT_SetInterruptHandler() method.
 *        This handler is called every time the RFINT ISR is executed. 
 * @pre Pins intializer called
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
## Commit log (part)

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2025-11-21 Add remote and firmware
2025-11-21 Replace RF module, finish routing
2025-11-21 Fix workflow setup
2025-11-21 Update xc8 URL
2025-11-21 Add checkout steps to KiCAD CI
2025-11-21 XC8 download experiments
2025-11-21 Fix ERC
2025-11-21 Quiet CI and fix ERCs
2025-11-21 Fix DRC and remove cmake parallel
2025-11-21 Fix cmake invocation
2025-11-22 Use XC setup action
2025-11-22 Fix cmake build
2025-11-22 Try manual cmake config
2025-11-22 Add generated config, download packs
2025-11-22 Fix pack folder permissions
2025-11-22 Use runner cmake
2025-12-20 New board rev, frist draft of ESPHome component
2025-12-20 Pull BQ25628E directly from GitHub
2025-12-20 Fix syntax
2025-12-20 One more time
2025-12-20 Finally correct syntax
2025-12-20 Fix dependencies
2025-12-20 Fix Adafruit wrapper
2025-12-20 Rename method references
2025-12-20 Custom libs
2025-12-20 Sensor definition in init
2025-12-20 Fix method name
2025-12-21 Fix byte orders
2025-12-21 Add i2c debug logging
2025-12-21 Fix charger and fuel gauge registers
2025-12-21 Implement all functions and registers
2025-12-21 Fix register bug
2025-12-21 Correctly shift register values
2025-12-21 Improve debug log, init fuel gauge
2025-12-21 Fix headers
2025-12-21 Change method visibility
2025-12-21 Increase OVP threshold
2025-12-21 Fix IChgTerm calculation: 320 for 20mA with 25mΩ resistor
2025-12-21 Add verbose I2C write debugging to identify configuration failure point
2025-12-21 Add VBUS_OVP register readback verification
2025-12-21 Fix read_register_word_ call - use reference not pointer
2025-12-21 Add diagnostic readback for registers 0x0B-0x0D to investigate VAC_OVP fault
2025-12-21 Set VBUS_OVP to maximum (0xFF) to test if fault clears - chip masks to 0xF0 = 15.6V
2025-12-22 Clean up
2025-12-22 Clean more
2025-12-22 Fix fuel gauge I2C impl
2025-12-22 Fix temp offset
2025-12-22 Fix TSHUT issues
2025-12-22 Fix battery scaling factor
2025-12-22 Fix BQ fault registers
2025-12-22 VBUS status logging
2025-12-22 Add poor src logging
2025-12-22 Fix register maps (again)
2025-12-29 Revamp BQ and MAX IC libs, build on CI with esphome
2025-12-29 Update interrupt pin mapping
2025-12-29 Randomize secrets
2025-12-29 Fix base ERC, compile build artifacts
2025-12-29 Fix bin upload path and archive reports
2025-12-29 Fix paths
2025-12-29 Fix DRC violations
2025-12-29 Do not run DRC for base
2025-12-29 Compile correct artifacts
2026-01-01 Fix mask/flag register addresses
2026-01-01 Fix temp calculation
2026-01-01 Simplify setup routine
2026-01-01 Fix VINDPM calc
2026-01-01 Fix more calculation bugs
2026-01-01 Add guards to prevent repetitive messages
2026-01-01 Add TS debug logging
2026-01-01 Disable external ILIM
2026-01-01 Fix ILIM handling
2026-01-01 Better charge status debugging
2026-01-01 Fix register setups again
2026-01-02 Use proper I²C word write functions
2026-01-02 Fix register addresses and fuel gauge SN reading
2026-01-02 Use ESP-IDF library for RFM69W
2026-01-02 Align CI build
2026-01-02 Update schematics with latest findings
2026-01-02 Fix ADC readings
2026-01-02 Verbose logging for ADC debug
2026-01-02 Fix i2c bus spamming
2026-01-02 Improve debug logging
2026-01-03 Fix MAX SN reading and re-add deep sleep
2026-01-03 Get SN from MAX finally done
2026-01-04 MAX SN read
2026-01-04 Wait for MAX to indicate SN reading ready
2026-01-05 Increase ADC resolution
2026-01-19 Base board Rev3
2026-04-18 Update docs, fix fuel gauge issue
2026-04-27 Rev 4
2026-04-29 Fix battery soc and improve sleep behavior
2026-05-25 Add 30s bell press cooldown guard
    Prevents repeated triggers from sustained intercom line noise after
    RV1 replacement with fixed 4.7kΩ resistor. Uses last_bell_millis
    global (non-persistent, resets on cold boot) to reject re-triggers
    within 30 seconds of a real press.
2026-05-25 Fix stale timer comment (120s -> 300s, HA-controlled)

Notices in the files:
remote/firmware/mcc_generated_files/system/pins.h:
© [2025] Microchip Technology Inc. and its subsidiaries.
README.md:
License: CERN-OHL-W-2.0
